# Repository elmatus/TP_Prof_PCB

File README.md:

# TP Profesional Shield - Plataforma de salto para deportistas de alto rendimiento

Proyecto de módulo externo (Poncho) para la EDU-CIAA, para realizar una plataforma de salto para deportistas de alto rendimiento.

Al shield se le conectan un sensor de presión, fabricado con [velostat](https://multimedia.3m.com/mws/media/305240O/stock-de-hojas-velostat-termoconformables.PDF), y 4 [celdas de carga](https://articulo.mercadolibre.com.ar/MLA-663821121-sensor-peso-celda-de-carga-50kg-strain-gauge-itytarg-_JM?matt_tool=88481412&matt_word=&matt_source=google&matt_campaign_id=11618987428&matt_ad_group_id=113657532672&matt_match_type=&matt_network=g&matt_device=c&matt_creative=479785004862&matt_keyword=&matt_ad_position=&matt_ad_type=pla&matt_merchant_id=114357573&matt_product_id=MLA663821121&matt_product_partition_id=353037831509&matt_target_id=pla-353037831509&gclid=CjwKCAjwvMqDBhB8EiwA2iSmPG8QP4wqGcePy5q8MkOb08h_7rUS4AC1D4PRTktfBgIJxREkHsAo8xoCAmIQAvD_BwE). Además cuenta con un módulo [WiFi ESP8266](https://www.espressif.com/en/products/modules/esp8266).

<!---  --->

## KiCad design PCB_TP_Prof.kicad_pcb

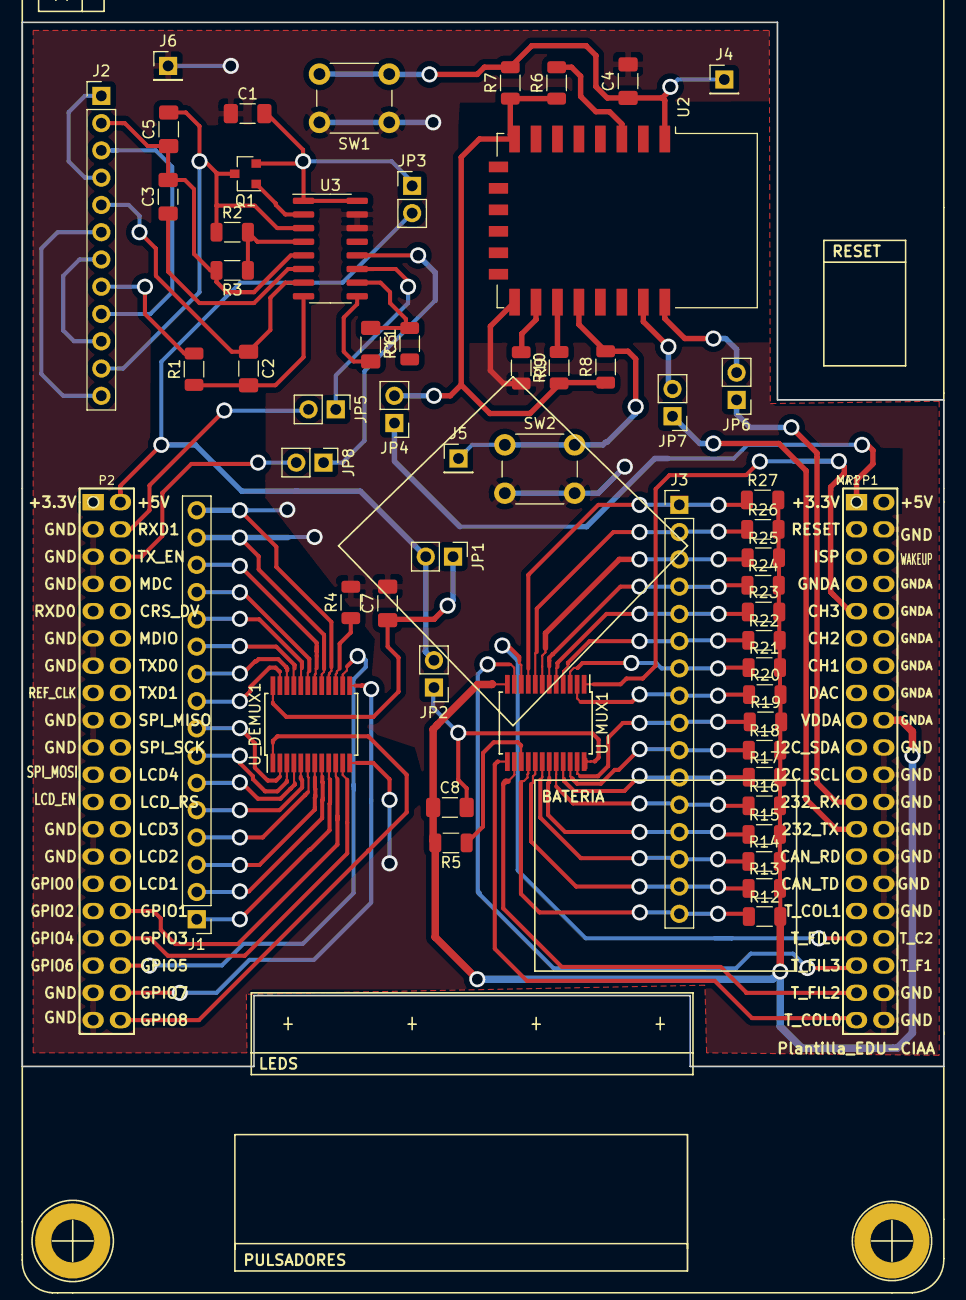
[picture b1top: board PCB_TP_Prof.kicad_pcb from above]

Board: 2 copper layers, 85.9 x 97.3 mm, 58 parts (0 on the bottom side), 77 nets.

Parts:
C1, C5: 10uF; C_1206_3216Metric_Pad1.33x1.80mm_HandSolder
C2, C3, C4, C6: 100nF; C_1206_3216Metric_Pad1.33x1.80mm_HandSolder
C7, C8: C; C_1206_3216Metric_Pad1.33x1.80mm_HandSolder
J1, J3: Conn_01x16_Female; PinHeader_1x16_P2.54mm_Vertical
J2: Conn_01x12_Female; PinHeader_1x12_P2.54mm_Vertical
J4, J5, J6: Conn_01x01_Male; PinHeader_1x01_P2.54mm_Vertical
JP1, JP2, JP3, JP4, JP5, JP6, JP7, JP8: Jumper; PinHeader_1x02_P2.54mm_Vertical
MP?: Plantilla_EDU-CIAA
Q1: Q_PNP_BEC; SOT-23
R1, R11: 1.2k; R_1206_3216Metric
R2: 20k; R_1206_3216Metric
R3: 8.2k; R_1206_3216Metric
R4, R5, R6, R7, R8, R9, R10: 10k; R_1206_3216Metric
R12, R13, R14, R15, R16, R17, R18, R19, R20, R21, R22, R23, R24, R25, R26, R27: 1k; R_1206_3216Metric
SW1, SW2: SW_Push; SW_PUSH_6mm
U2: ESP-12E
U3: HX711; SOP-16_3.9x9.9mm_P1.27mm
U_DEMUX1: CD74HC4067SM; SSOP-24_5.3x8.2mm_P0.65mm
U_MUX1: CD74HC4067SM; SSOP-24_5.3x8.2mm_P0.65mm
XA1: Conn_Poncho2P_2x_20x2; PonchoGrande_sinBorde_ConHuecos

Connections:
+3V3: JP4.1, XA1.1
+5V: JP1.2, JP2.2, JP3.2, XA1.42
/Conector-EDU_CIAA/232_RX: JP6.1, XA1.23
/Conector-EDU_CIAA/232_TX: JP7.1, XA1.25
/Conector-EDU_CIAA/CH3: U_MUX1.1, XA1.9
/Conector-EDU_CIAA/GPIO1: U_DEMUX1.10, XA1.72
/Conector-EDU_CIAA/GPIO3: U_DEMUX1.11, XA1.74
/Conector-EDU_CIAA/GPIO5: U_DEMUX1.14, XA1.76
/Conector-EDU_CIAA/GPIO7: U_DEMUX1.13, XA1.78
/Conector-EDU_CIAA/GPIO8: U_DEMUX1.1, XA1.80
/Conector-EDU_CIAA/RXD1-GPIO21: JP5.2, XA1.44
/Conector-EDU_CIAA/TX_EN-GPIO19: JP8.2, XA1.46
/Conector-EDU_CIAA/T_COL0-GPIO29: U_MUX1.13, XA1.39
/Conector-EDU_CIAA/T_FIL0-GPIO25: U_MUX1.10, XA1.33
/Conector-EDU_CIAA/T_FIL2-GPIO27: U_MUX1.14, XA1.37
/Conector-EDU_CIAA/T_FIL3-GPIO28: U_MUX1.11, XA1.35
/HX711/A+: J2.8, R1.2
/HX711/A-: C2.1, J2.5, U3.7
/HX711/B-: C6.2, U3.9
/HX711/DT: JP8.1, U3.12
/HX711/E+: C5.2, J2.11, Q1.3, R2.1, U3.3
/HX711/E-: C3.2, C5.1, J2.2, R3.2, U3.5
/HX711/SCK: JP5.1, U3.11
/HX711/VCC: C1.2, JP3.1, Q1.2, U3.1, U3.16
/NodeMCU/+3V3: JP4.2, R6.1, R7.1, R8.1, R10.1, U2.8
/NodeMCU/GPIO0-D3: J5.1, R8.2, SW2.1, U2.18
/NodeMCU/RST: C4.1, J4.1, R7.2, SW1.2, U2.1
/NodeMCU/RX: JP7.2, U2.21
/NodeMCU/TX: JP6.2, U2.22
GND: C1.1, C4.2, C7.2, J1.15, J1.16, J6.1, R4.2, R9.2, SW1.1, SW2.2, U2.15, U3.14, U3.15, U_DEMUX1.12, U_DEMUX1.16, U_DEMUX1.17, XA1.4, XA1.20, XA1.22, XA1.24, XA1.26, XA1.28, XA1.30, XA1.32, XA1.38, XA1.40, XA1.43, XA1.45, XA1.47, XA1.51, XA1.53, XA1.57, XA1.59, XA1.65, XA1.67, XA1.77, XA1.79
GNDA: C8.1, R5.2, R12.2, R13.2, R14.2, R15.2, R16.2, R17.2, R18.2, R19.2, R20.2, R21.2, R22.2, R23.2, R24.2, R25.2, R26.2, R27.2, U_MUX1.12, XA1.18
unnamed: C2.2, R1.1, U3.8
unnamed: C3.1, U3.6
unnamed: C6.1, R11.2, U3.10
unnamed: C7.1, JP1.1, U_DEMUX1.24
unnamed: C8.2, JP2.1, U_MUX1.24
unnamed: J1.1, U_DEMUX1.9
unnamed: J1.2, U_DEMUX1.8
unnamed: J1.3, U_DEMUX1.7
unnamed: J1.4, U_DEMUX1.6
unnamed: J1.5, U_DEMUX1.5
unnamed: J1.6, U_DEMUX1.4
unnamed: J1.7, U_DEMUX1.3
unnamed: J1.8, U_DEMUX1.2
unnamed: J1.9, U_DEMUX1.23
unnamed: J1.10, U_DEMUX1.22
unnamed: J1.11, U_DEMUX1.21
unnamed: J1.12, U_DEMUX1.20
unnamed: J1.13, U_DEMUX1.19
unnamed: J1.14, U_DEMUX1.18
unnamed: J2.1, J2.4
unnamed: J2.3, J2.9
unnamed: J2.7, J2.10
unnamed: J2.6, J2.12
unnamed: J3.1, R27.1, U_MUX1.9
unnamed: J3.2, R26.1, U_MUX1.8
unnamed: J3.3, R25.1, U_MUX1.7
unnamed: J3.4, R24.1, U_MUX1.6
unnamed: J3.5, R23.1, U_MUX1.5
unnamed: J3.6, R22.1, U_MUX1.4
unnamed: J3.7, R21.1, U_MUX1.3
unnamed: J3.8, R20.1, U_MUX1.2
unnamed: J3.9, R19.1, U_MUX1.23
unnamed: J3.10, R18.1, U_MUX1.22
unnamed: J3.11, R17.1, U_MUX1.21
unnamed: J3.12, R16.1, U_MUX1.20
unnamed: J3.13, R15.1, U_MUX1.19
unnamed: J3.14, R14.1, U_MUX1.18
unnamed: J3.15, R13.1, U_MUX1.17
unnamed: J3.16, R12.1, U_MUX1.16
unnamed: Q1.1, U3.2
unnamed: R2.2, R3.1, U3.4
unnamed: R4.1, U_DEMUX1.15
unnamed: R5.1, U_MUX1.15
unnamed: R6.2, U2.3
unnamed: R9.1, U2.16
unnamed: R10.2, U2.17

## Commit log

2021-02-20 update files
2021-04-09 Update files + gerbers
2021-04-11 Update files final
2021-04-11 Update gerbers
2021-04-12 Ultimos detalles
2021-04-12 imagen 3d
2021-04-14 Rotulo y BOM
